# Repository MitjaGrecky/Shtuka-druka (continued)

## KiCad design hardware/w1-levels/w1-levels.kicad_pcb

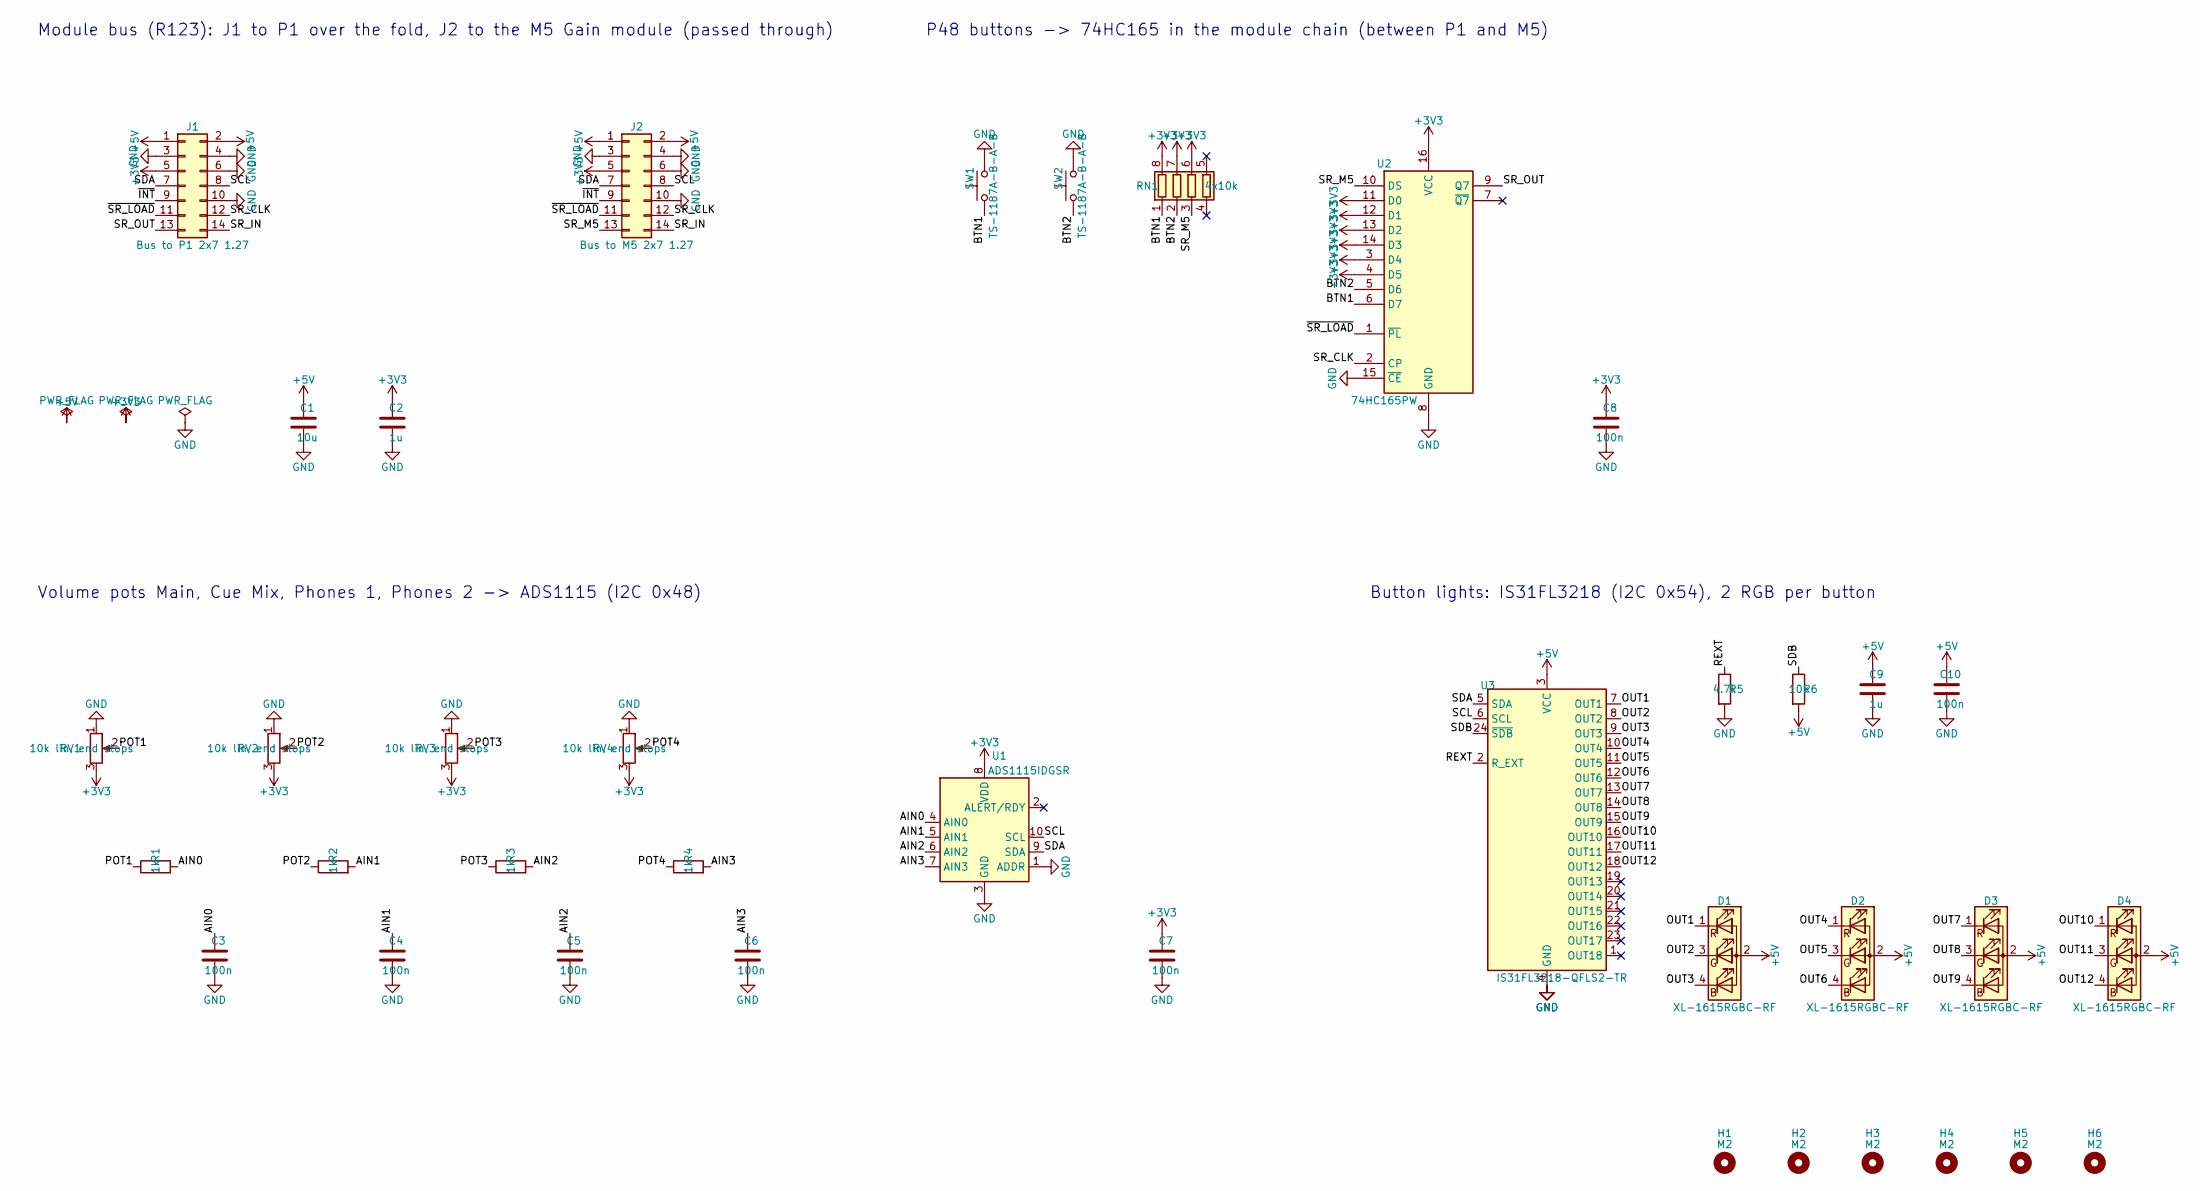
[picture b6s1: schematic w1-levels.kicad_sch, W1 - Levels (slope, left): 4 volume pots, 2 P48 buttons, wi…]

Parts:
C1: 10u; C_0805_2012Metric; LCSC C15850
C2, C9: 1u; C_0402_1005Metric; LCSC C52923
C3, C4, C5, C6, C7, C8, C10: 100n; C_0402_1005Metric; LCSC C1525
D1, D2, D3, D4: XL-1615RGBC-RF; LED_RGB_XL-1615RGBC_1.6x1.5mm; LCSC C965840
H1, H2, H3, H4, H5, H6: M2; MountingHole_2.2mm_M2
J1: Bus to P1 2x7 1.27; PinHeader_2x07_P1.27mm_Vertical; LCSC C5372811
J2: Bus to M5 2x7 1.27; PinHeader_2x07_P1.27mm_Vertical; LCSC C5372811
R1, R2, R3, R4: 1k; R_0402_1005Metric; LCSC C11702
R5: 4.7k; R_0402_1005Metric; LCSC C25900
R6: 10k; R_0402_1005Metric; LCSC C25744
RN1: 4x10k; R_Array_Convex_4x0402; LCSC C25725
RV1, RV2, RV3, RV4: 10k lin, end stops; Potentiometer_Alps_RK09K_Single_Vertical; Part Alps RK09K1130A6S or another RK09K 10k 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; LCSC C209770
SW1, SW2: TS-1187A-B-A-B; SW_Push_1P1T_XKB_TS-1187A; LCSC C318884
U1: ADS1115IDGSR; TSSOP-10_3x3mm_P0.5mm; LCSC C37593
U2: 74HC165PW; TSSOP-16_4.4x5mm_P0.65mm; LCSC C80696
U3: IS31FL3218-QFLS2-TR; QFN-24-1EP_4x4mm_P0.5mm_EP2.7x2.7mm; LCSC C2940546

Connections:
+3V3: C2.1, C7.1, C8.1, J1.5, J2.5, RN1.6 (R3.2), RN1.7 (R2.2), RN1.8 (R1.2), RV1.3, RV2.3, RV3.3, RV4.3, U1.8 (VDD), U2.3 (D4), U2.4 (D5), U2.11 (D0), U2.12 (D1), U2.13 (D2), U2.14 (D3), U2.16 (VCC)
+5V: C1.1, C9.1, C10.1, D1.2 (A), D2.2 (A), D3.2 (A), D4.2 (A), J1.1, J1.2, J2.1, J2.2, R6.2, U3.3 (VCC)
/AIN0: C3.1, R1.2, U1.4 (AIN0)
/AIN1: C4.1, R2.2, U1.5 (AIN1)
/AIN2: C5.1, R3.2, U1.6 (AIN2)
/AIN3: C6.1, R4.2, U1.7 (AIN3)
/BTN1: RN1.1 (R1.1), SW1.1, U2.6 (D7)
/BTN2: RN1.2 (R2.1), SW2.1, U2.5 (D6)
/OUT1: D1.1 (RK), U3.7 (OUT1)
/OUT2: D1.3 (GK), U3.8 (OUT2)
/OUT3: D1.4 (BK), U3.9 (OUT3)
/OUT4: D2.1 (RK), U3.10 (OUT4)
/OUT5: D2.3 (GK), U3.11 (OUT5)
/OUT6: D2.4 (BK), U3.12 (OUT6)
/OUT7: D3.1 (RK), U3.13 (OUT7)
/OUT8: D3.3 (GK), U3.14 (OUT8)
/OUT9: D3.4 (BK), U3.15 (OUT9)
/OUT10: D4.1 (RK), U3.16 (OUT10)
/OUT11: D4.3 (GK), U3.17 (OUT11)
/OUT12: D4.4 (BK), U3.18 (OUT12)
/POT1: R1.1, RV1.2
/POT2: R2.1, RV2.2
/POT3: R3.1, RV3.2
/POT4: R4.1, RV4.2
/REXT: R5.1, U3.2 (R_EXT)
/SCL: J1.8, J2.8, U1.10 (SCL), U3.6 (SCL)
/SDA: J1.7, J2.7, U1.9 (SDA), U3.5 (SDA)
/SDB: R6.1, U3.24 (~SDB)
/SR_CLK: J1.12, J2.12, U2.2 (CP)
/SR_IN: J1.14, J2.14
/SR_M5: J2.13, RN1.3 (R3.1), U2.10 (DS)
/SR_OUT: J1.13, U2.9 (Q7)
/~INT: J1.9, J2.9
/~SR_LOAD: J1.11, J2.11, U2.1 (~PL)
GND: C1.2, C2.2, C3.2, C4.2, C5.2, C6.2, C7.2, C8.2, C9.2, C10.2, J1.3, J1.4, J1.6, J1.10, J2.3, J2.4, J2.6, J2.10, R5.2, RV1.1, RV2.1, RV3.1, RV4.1, SW1.2, SW2.2, U1.1 (ADDR), U1.3 (GND), U2.8 (GND), U2.15 (~CE), U3.4 (GND), U3.25 (GND)

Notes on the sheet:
Module bus (R123): J1 to P1 over the fold, J2 to the M5 Gain module (passed through)
Volume pots Main, Cue Mix, Phones 1, Phones 2 -> ADS1115 (I2C 0x48)
P48 buttons -> 74HC165 in the module chain (between P1 and M5)
Button lights: IS31FL3218 (I2C 0x54), 2 RGB per button

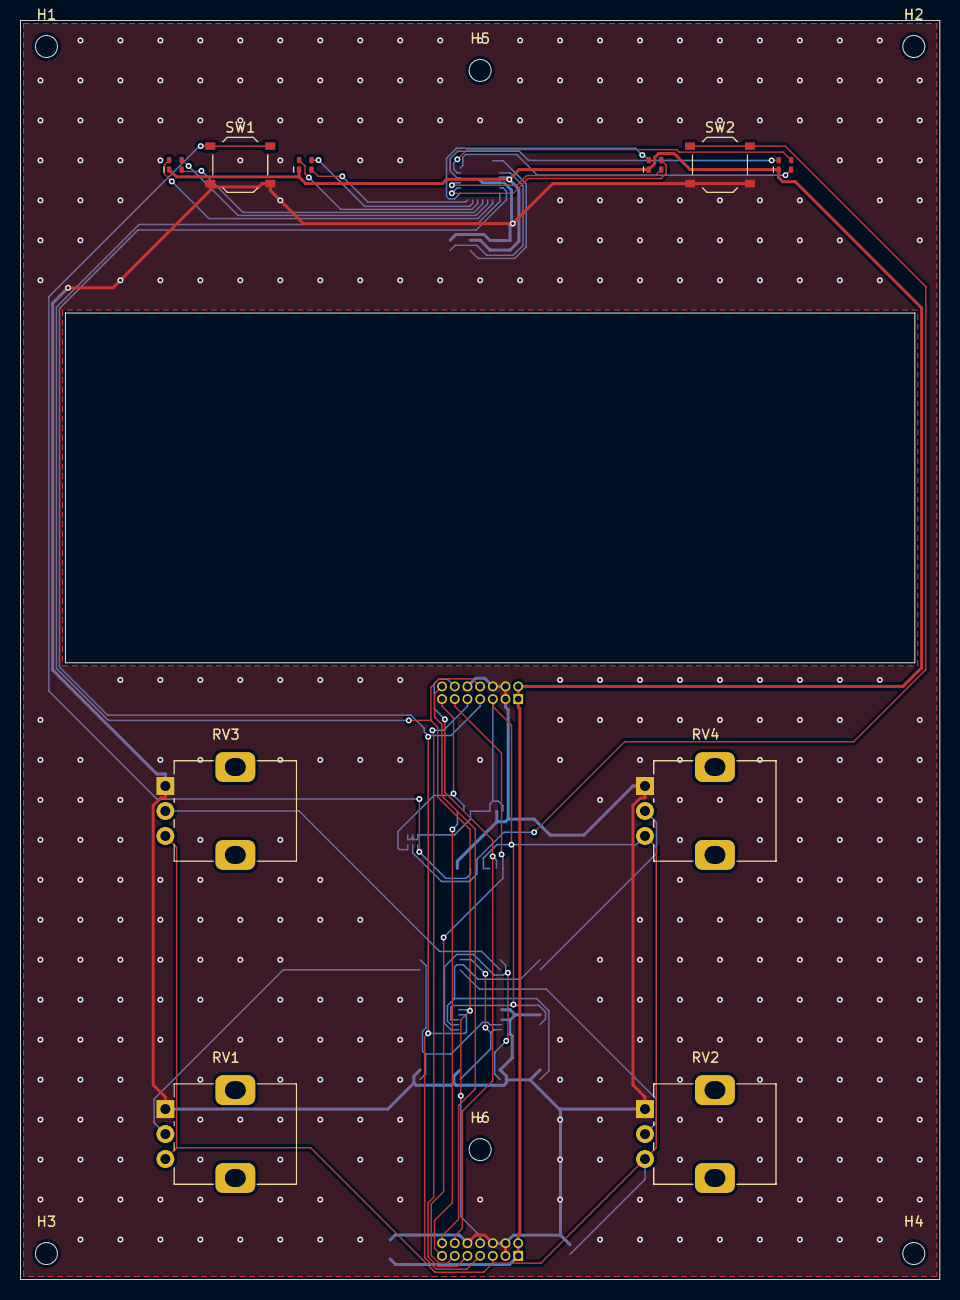
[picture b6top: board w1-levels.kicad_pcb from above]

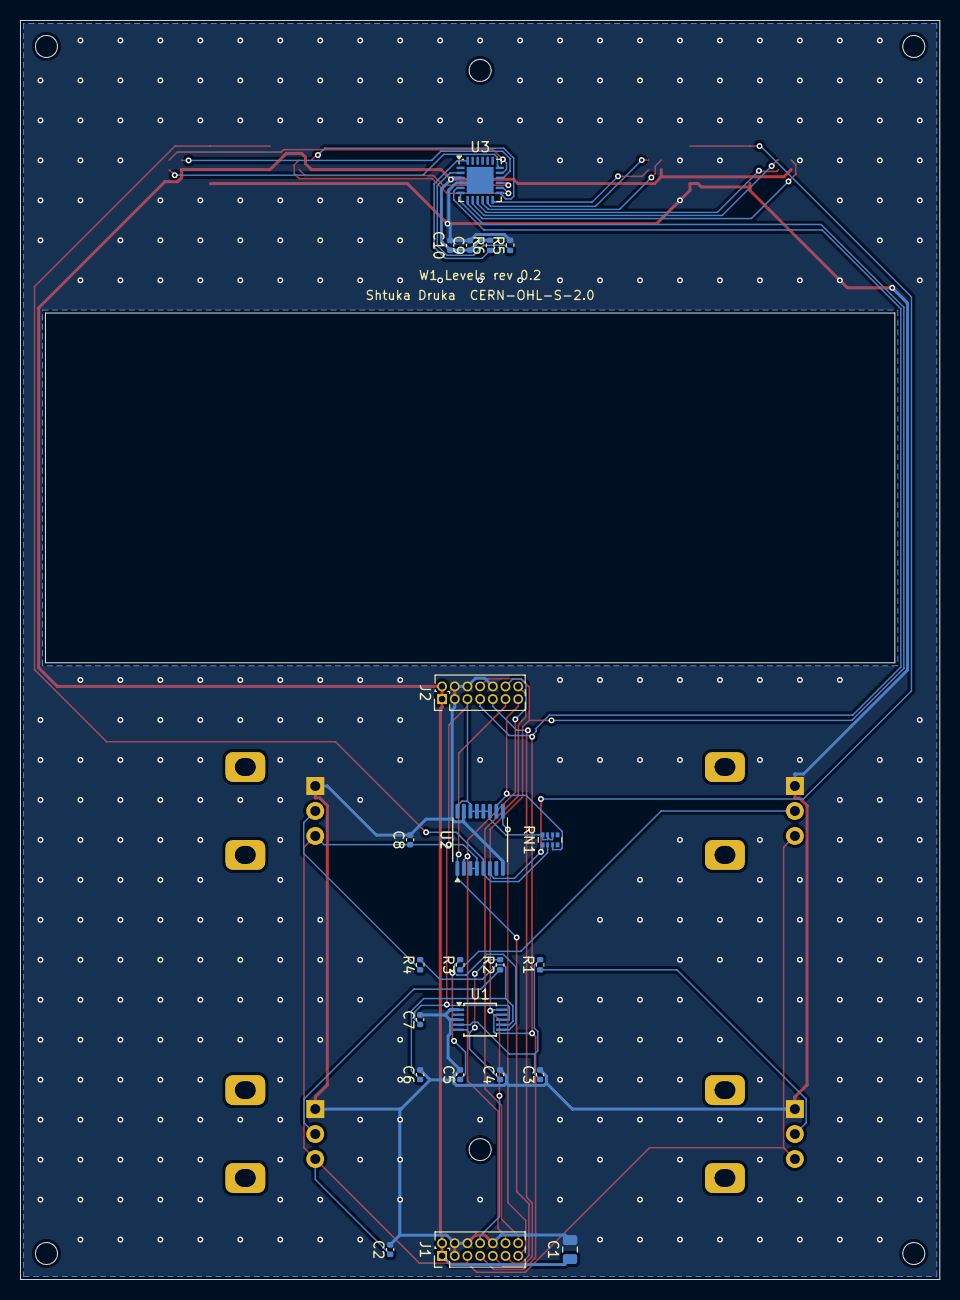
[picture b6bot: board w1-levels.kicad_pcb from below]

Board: 2 copper layers, 92.0 x 126.0 mm, 38 parts (22 on the bottom side), 35 nets.

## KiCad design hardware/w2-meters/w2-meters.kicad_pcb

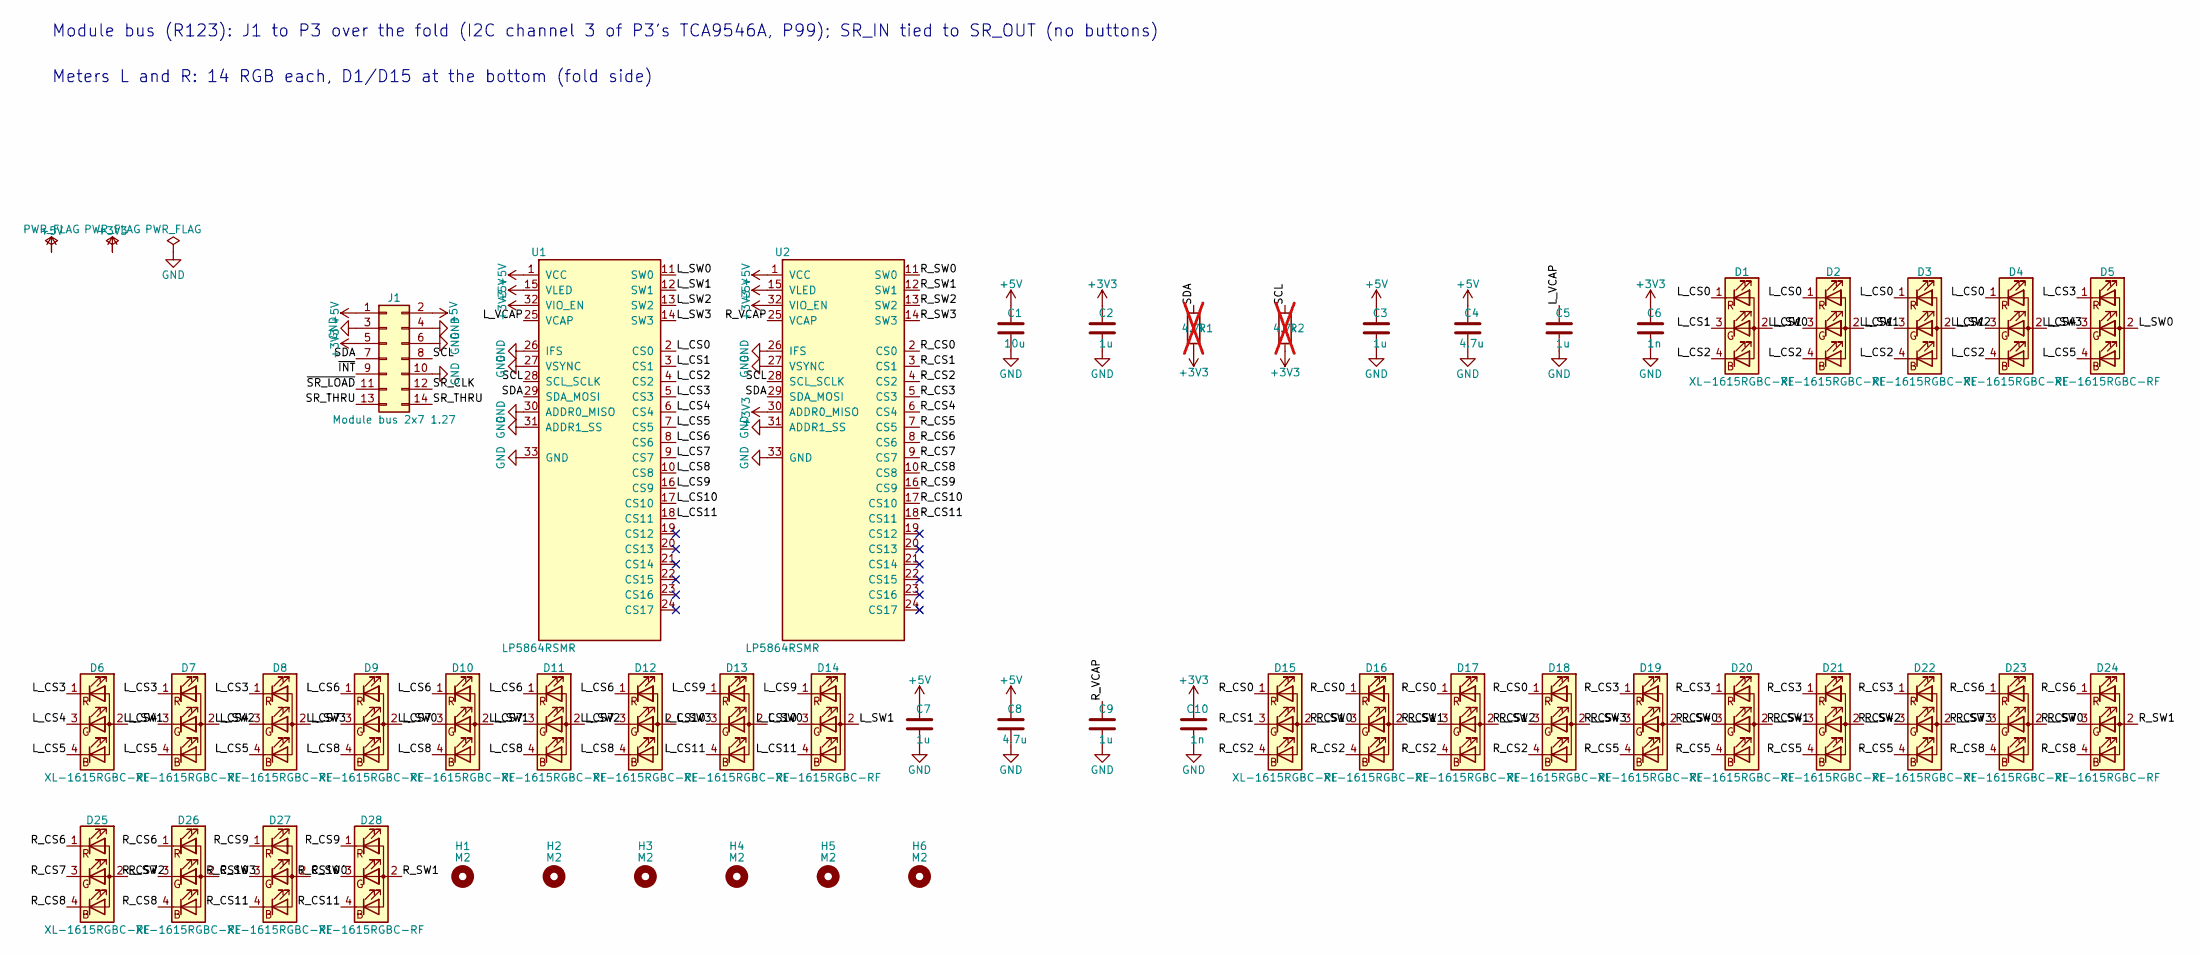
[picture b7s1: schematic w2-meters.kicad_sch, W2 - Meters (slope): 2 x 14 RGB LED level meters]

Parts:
C1: 10u; C_0805_2012Metric; LCSC C15850
C2, C3, C5, C7, C9: 1u; C_0402_1005Metric; LCSC C52923
C4, C8: 4.7u; C_0805_2012Metric; LCSC C1779
C6, C10: 1n; C_0402_1005Metric; LCSC C1523
D1, D2, D3, D4, D5, D6, D7, D8, D9, D10, D11, D12, D13, D14, D15, D16, D17, D18, D19, D20, D21, D22, D23, D24, D25, D26, D27, D28: XL-1615RGBC-RF; LED_RGB_XL-1615RGBC_1.6x1.5mm; LCSC C965840
H1, H2, H3, H4, H5, H6: M2; MountingHole_2.2mm_M2
J1: Module bus 2x7 1.27; PinHeader_2x07_P1.27mm_Vertical; LCSC C5372811
R1, R2: 4.7k; R_0402_1005Metric; LCSC C25900; not fitted
U1, U2: LP5864RSMR; VQFN-32-1EP_4x4mm_P0.4mm_EP2.8x2.8mm; LCSC C5220564

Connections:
+3V3: C2.1, C6.1, C10.1, J1.5, R1.2, R2.2, U1.32 (VIO_EN), U2.30 (ADDR0_MISO), U2.32 (VIO_EN)
+5V: C1.1, C3.1, C4.1, C7.1, C8.1, J1.1, J1.2, U1.1 (VCC), U1.15 (VLED), U2.1 (VCC), U2.15 (VLED)
/L_CS0: D1.1 (RK), D2.1 (RK), D3.1 (RK), D4.1 (RK), U1.2 (CS0)
/L_CS1: D1.3 (GK), D2.3 (GK), D3.3 (GK), D4.3 (GK), U1.3 (CS1)
/L_CS2: D1.4 (BK), D2.4 (BK), D3.4 (BK), D4.4 (BK), U1.4 (CS2)
/L_CS3: D5.1 (RK), D6.1 (RK), D7.1 (RK), D8.1 (RK), U1.5 (CS3)
/L_CS4: D5.3 (GK), D6.3 (GK), D7.3 (GK), D8.3 (GK), U1.6 (CS4)
/L_CS5: D5.4 (BK), D6.4 (BK), D7.4 (BK), D8.4 (BK), U1.7 (CS5)
/L_CS6: D9.1 (RK), D10.1 (RK), D11.1 (RK), D12.1 (RK), U1.8 (CS6)
/L_CS7: D9.3 (GK), D10.3 (GK), D11.3 (GK), D12.3 (GK), U1.9 (CS7)
/L_CS8: D9.4 (BK), D10.4 (BK), D11.4 (BK), D12.4 (BK), U1.10 (CS8)
/L_CS9: D13.1 (RK), D14.1 (RK), U1.16 (CS9)
/L_CS10: D13.3 (GK), D14.3 (GK), U1.17 (CS10)
/L_CS11: D13.4 (BK), D14.4 (BK), U1.18 (CS11)
/L_SW0: D1.2 (A), D5.2 (A), D9.2 (A), D13.2 (A), U1.11 (SW0)
/L_SW1: D2.2 (A), D6.2 (A), D10.2 (A), D14.2 (A), U1.12 (SW1)
/L_SW2: D3.2 (A), D7.2 (A), D11.2 (A), U1.13 (SW2)
/L_SW3: D4.2 (A), D8.2 (A), D12.2 (A), U1.14 (SW3)
/L_VCAP: C5.1, U1.25 (VCAP)
/R_CS0: D15.1 (RK), D16.1 (RK), D17.1 (RK), D18.1 (RK), U2.2 (CS0)
/R_CS1: D15.3 (GK), D16.3 (GK), D17.3 (GK), D18.3 (GK), U2.3 (CS1)
/R_CS2: D15.4 (BK), D16.4 (BK), D17.4 (BK), D18.4 (BK), U2.4 (CS2)
/R_CS3: D19.1 (RK), D20.1 (RK), D21.1 (RK), D22.1 (RK), U2.5 (CS3)
/R_CS4: D19.3 (GK), D20.3 (GK), D21.3 (GK), D22.3 (GK), U2.6 (CS4)
/R_CS5: D19.4 (BK), D20.4 (BK), D21.4 (BK), D22.4 (BK), U2.7 (CS5)
/R_CS6: D23.1 (RK), D24.1 (RK), D25.1 (RK), D26.1 (RK), U2.8 (CS6)
/R_CS7: D23.3 (GK), D24.3 (GK), D25.3 (GK), D26.3 (GK), U2.9 (CS7)
/R_CS8: D23.4 (BK), D24.4 (BK), D25.4 (BK), D26.4 (BK), U2.10 (CS8)
/R_CS9: D27.1 (RK), D28.1 (RK), U2.16 (CS9)
/R_CS10: D27.3 (GK), D28.3 (GK), U2.17 (CS10)
/R_CS11: D27.4 (BK), D28.4 (BK), U2.18 (CS11)
/R_SW0: D15.2 (A), D19.2 (A), D23.2 (A), D27.2 (A), U2.11 (SW0)
/R_SW1: D16.2 (A), D20.2 (A), D24.2 (A), D28.2 (A), U2.12 (SW1)
/R_SW2: D17.2 (A), D21.2 (A), D25.2 (A), U2.13 (SW2)
/R_SW3: D18.2 (A), D22.2 (A), D26.2 (A), U2.14 (SW3)
/R_VCAP: C9.1, U2.25 (VCAP)
/SCL: J1.8, R2.1, U1.28 (SCL_SCLK), U2.28 (SCL_SCLK)
/SDA: J1.7, R1.1, U1.29 (SDA_MOSI), U2.29 (SDA_MOSI)
/SR_CLK: J1.12
/SR_THRU: J1.13, J1.14
/~INT: J1.9
/~SR_LOAD: J1.11
GND: C1.2, C2.2, C3.2, C4.2, C5.2, C6.2, C7.2, C8.2, C9.2, C10.2, J1.3, J1.4, J1.6, J1.10, U1.26 (IFS), U1.27 (VSYNC), U1.30 (ADDR0_MISO), U1.31 (ADDR1_SS), U1.33 (GND), U2.26 (IFS), U2.27 (VSYNC), U2.31 (ADDR1_SS), U2.33 (GND)

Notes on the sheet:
Module bus (R123): J1 to P3 over the fold (I2C channel 3 of P3's TCA9546A, P99); SR_IN tied to SR_OUT (no buttons)
Meters L and R: 14 RGB each, D1/D15 at the bottom (fold side)

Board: 2 copper layers, 49 parts (15 on the bottom side), 40 nets, no tracks yet.

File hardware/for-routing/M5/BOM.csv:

Comment,Designator,Footprint,LCSC Part #
Module bus 2x7 1.27,J1,PinHeader_2x07_P1.27mm_Vertical,C3975190
10u,C1,C_0805_2012Metric,C15850
1u,"C2,C3,C5",C_0402_1005Metric,C52923
10k,R3,R_0402_1005Metric,C25744
LP5864RSMR,U1,VQFN-32-1EP_4x4mm_P0.4mm_EP2.8x2.8mm,C5220564
4.7u,C4,C_0805_2012Metric,
1n,C6,C_0402_1005Metric,
XL-1615RGBC-RF,"D1,D2,D3,D4,D5,D6,D7,D8,D9,D10,D11,D12,D13,D14,D15,D16,D17,D18,D19,D20,D21,D22,D23,D24",LED_RGB_XL-1615RGBC_1.6x1.5mm,C965840
74HC165PW,U2,TSSOP-16_4.4x5mm_P0.65mm,C80696
100n,C7,C_0402_1005Metric,C1525
4x10k,"RN1,RN2",R_Array_Convex_4x0402,C25725
"EC11E smooth, switch","ENC1,ENC2",RotaryEncoder_Alps_EC11E-Switch_Vertical_H20mm_Ring,

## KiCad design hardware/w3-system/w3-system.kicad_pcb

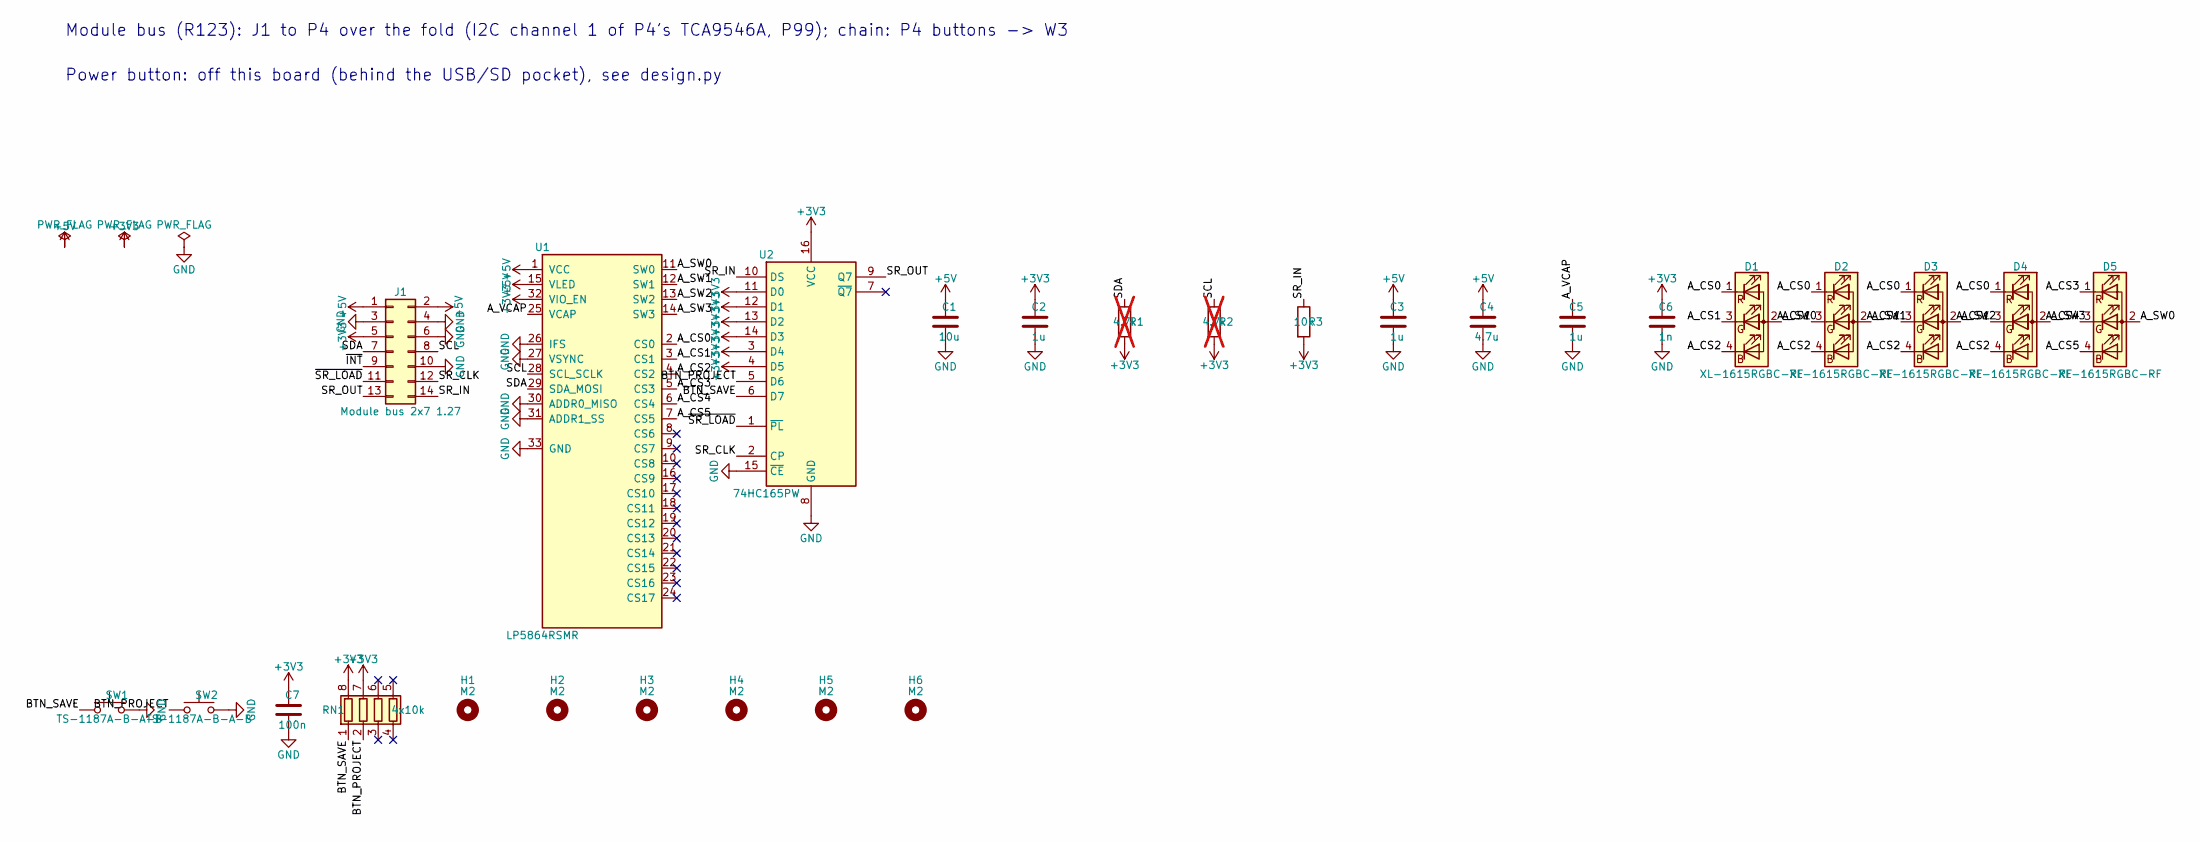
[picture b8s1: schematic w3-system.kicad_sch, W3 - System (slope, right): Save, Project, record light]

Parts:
C1: 10u; C_0805_2012Metric; LCSC C15850
C2, C3, C5: 1u; C_0402_1005Metric; LCSC C52923
C4: 4.7u; C_0805_2012Metric; LCSC C1779
C6: 1n; C_0402_1005Metric; LCSC C1523
C7: 100n; C_0402_1005Metric; LCSC C1525
D1, D2, D3, D4, D5: XL-1615RGBC-RF; LED_RGB_XL-1615RGBC_1.6x1.5mm; LCSC C965840
H1, H2, H3, H4, H5, H6: M2; MountingHole_2.2mm_M2
J1: Module bus 2x7 1.27; PinHeader_2x07_P1.27mm_Vertical; LCSC C5372811
R1, R2: 4.7k; R_0402_1005Metric; LCSC C25900; not fitted
R3: 10k; R_0402_1005Metric; LCSC C25744
RN1: 4x10k; R_Array_Convex_4x0402; LCSC C25725
SW1, SW2: TS-1187A-B-A-B; SW_Push_1P1T_XKB_TS-1187A; LCSC C318884
U1: LP5864RSMR; VQFN-32-1EP_4x4mm_P0.4mm_EP2.8x2.8mm; LCSC C5220564
U2: 74HC165PW; TSSOP-16_4.4x5mm_P0.65mm; LCSC C80696

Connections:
+3V3: C2.1, C6.1, C7.1, J1.5, R1.2, R2.2, R3.2, RN1.7 (R2.2), RN1.8 (R1.2), U1.32 (VIO_EN), U2.3 (D4), U2.4 (D5), U2.11 (D0), U2.12 (D1), U2.13 (D2), U2.14 (D3), U2.16 (VCC)
+5V: C1.1, C3.1, C4.1, J1.1, J1.2, U1.1 (VCC), U1.15 (VLED)
/A_CS0: D1.1 (RK), D2.1 (RK), D3.1 (RK), D4.1 (RK), U1.2 (CS0)
/A_CS1: D1.3 (GK), D2.3 (GK), D3.3 (GK), D4.3 (GK), U1.3 (CS1)
/A_CS2: D1.4 (BK), D2.4 (BK), D3.4 (BK), D4.4 (BK), U1.4 (CS2)
/A_CS3: D5.1 (RK), U1.5 (CS3)
/A_CS4: D5.3 (GK), U1.6 (CS4)
/A_CS5: D5.4 (BK), U1.7 (CS5)
/A_SW0: D1.2 (A), D5.2 (A), U1.11 (SW0)
/A_SW1: D2.2 (A), U1.12 (SW1)
/A_SW2: D3.2 (A), U1.13 (SW2)
/A_SW3: D4.2 (A), U1.14 (SW3)
/A_VCAP: C5.1, U1.25 (VCAP)
/BTN_PROJECT: RN1.2 (R2.1), SW2.1, U2.5 (D6)
/BTN_SAVE: RN1.1 (R1.1), SW1.1, U2.6 (D7)
/SCL: J1.8, R2.1, U1.28 (SCL_SCLK)
/SDA: J1.7, R1.1, U1.29 (SDA_MOSI)
/SR_CLK: J1.12, U2.2 (CP)
/SR_IN: J1.14, R3.1, U2.10 (DS)
/SR_OUT: J1.13, U2.9 (Q7)
/~INT: J1.9
/~SR_LOAD: J1.11, U2.1 (~PL)
GND: C1.2, C2.2, C3.2, C4.2, C5.2, C6.2, C7.2, J1.3, J1.4, J1.6, J1.10, SW1.2, SW2.2, U1.26 (IFS), U1.27 (VSYNC), U1.30 (ADDR0_MISO), U1.31 (ADDR1_SS), U1.33 (GND), U2.8 (GND), U2.15 (~CE)

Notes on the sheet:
Module bus (R123): J1 to P4 over the fold (I2C channel 1 of P4's TCA9546A, P99); chain: P4 buttons -> W3
Power button: off this board (behind the USB/SD pocket), see design.py

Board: 2 copper layers, 27 parts (14 on the bottom side), 22 nets, no tracks yet.
